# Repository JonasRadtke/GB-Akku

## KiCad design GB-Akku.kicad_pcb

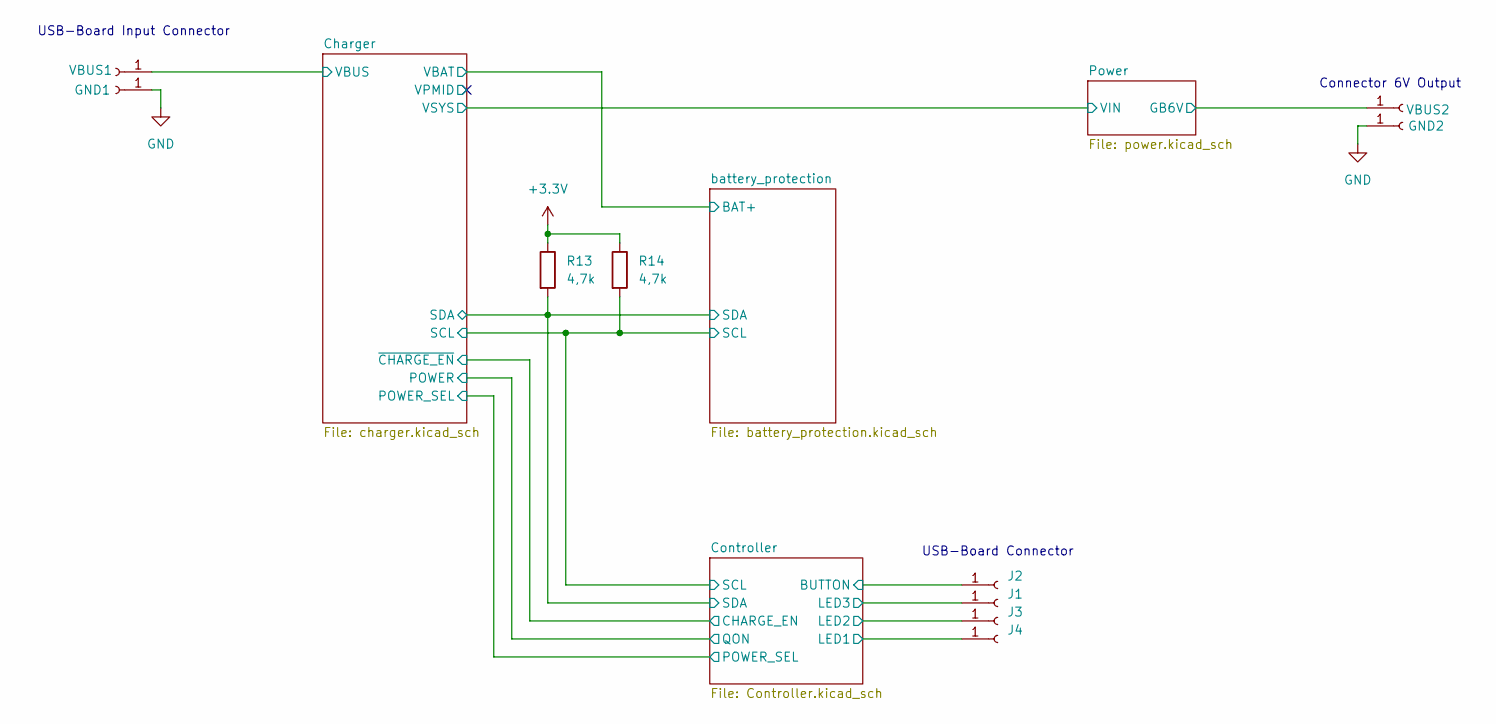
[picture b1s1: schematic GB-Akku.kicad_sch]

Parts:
GND1, GND2: +; SolderWire-0.25sqmm_1x01_D0.65mm_OD1.7mm
J1, J2, J3, J4: Conn_01x01_Socket; SolderWire-0.1sqmm_1x01_D0.4mm_OD1mm
R13, R14: 4,7k; R_0603_1608Metric
VBUS1, VBUS2: +; SolderWire-0.25sqmm_1x01_D0.65mm_OD1.7mm

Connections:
+3.3V: R13.1, R14.1; also elsewhere on the board
+6V: VBUS2.1; also elsewhere on the board
/Charger/SCL: R14.2; also elsewhere on the board
/Charger/SDA: R13.2; also elsewhere on the board
/Charger/VBUS: VBUS1.1; also elsewhere on the board
/Controller/BUTTON: J2.1; also elsewhere on the board
/Controller/LED1: J4.1; also elsewhere on the board
/Controller/LED2: J3.1; also elsewhere on the board
/Controller/LED3: J1.1; also elsewhere on the board
GND: GND1.1, GND2.1; also elsewhere on the board

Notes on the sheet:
Connector 6V Output
USB-Board Input Connector
USB-Board Connector

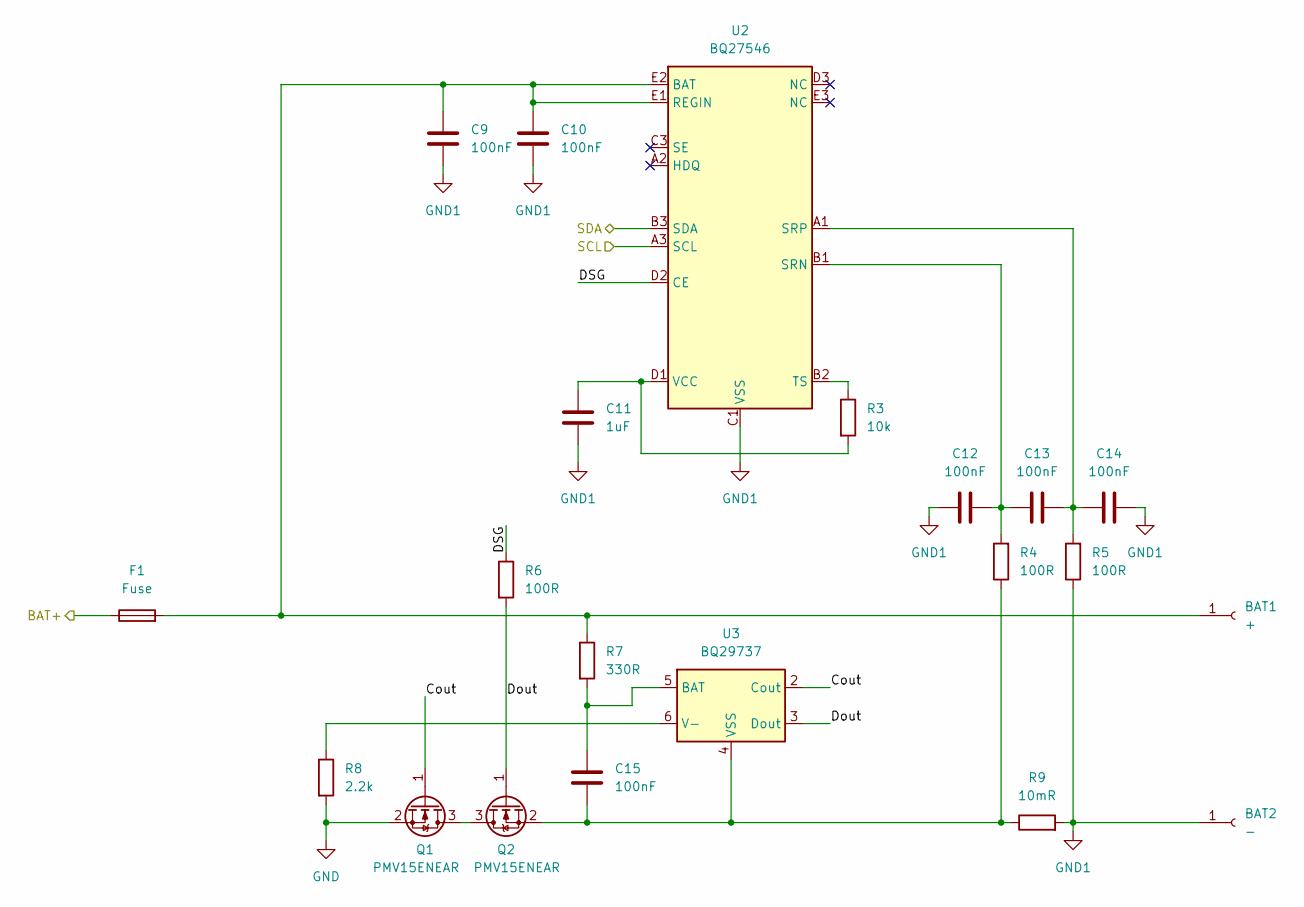
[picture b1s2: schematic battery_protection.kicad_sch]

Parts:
BAT1: +; SolderWire-0.5sqmm_1x01_D0.9mm_OD2.1mm
BAT2: -; SolderWire-0.5sqmm_1x01_D0.9mm_OD2.1mm
C9, C10, C12, C13, C14, C15: 100nF; C_0603_1608Metric
C11: 1uF; C_0603_1608Metric
F1: Fuse; Fuse_1206_3216Metric
Q1, Q2: PMV15ENEAR; SOT-23
R3: 10k; R_0603_1608Metric
R4, R5, R6: 100R; R_0603_1608Metric
R7: 330R; R_0603_1608Metric
R8: 2.2k; R_0603_1608Metric
R9: 10mR; R_0805_2012Metric
U2: BQ27546; DSBGA-15_1.95x2.6mm_P0.5mm_special
U3: BQ29737; WSON-6_1.5x1.5mm_P0.5mm

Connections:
/Charger/SCL: U2.A3 (SCL); also elsewhere on the board
/Charger/SDA: U2.B3 (SDA); also elsewhere on the board
/battery_protection/Cout: Q1.1 (G), U3.2 (Cout)
/battery_protection/DSG: R6.1, U2.D2 (CE)
/battery_protection/Dout: Q2.1 (G), R6.2, U3.3 (Dout)
BAT: F1.1; also elsewhere on the board
GND: Q1.2 (S), R8.2; also elsewhere on the board
GND1: BAT2.1, C9.2, C10.2, C11.2, C12.1, C14.2, R5.1, R9.2, U2.C1 (VSS), U2.C2 (VSS)
unnamed: BAT1.1, C9.1, C10.1, F1.2, R7.1, U2.E1 (REGIN), U2.E2 (BAT)
unnamed: Q1.3 (D), Q2.3 (D)
unnamed: C15.2, Q2.2 (S), R4.1, R9.1, U3.4 (VSS)
unnamed: C12.2, C13.1, R4.2, U2.B1 (SRN)
unnamed: C13.2, C14.1, R5.2, U2.A1 (SRP)
unnamed: R3.1, U2.B2 (TS)
unnamed: C11.1, R3.2, U2.D1 (VCC)
unnamed: C15.1, R7.2, U3.5 (BAT)
unnamed: R8.1, U3.6 (V-)

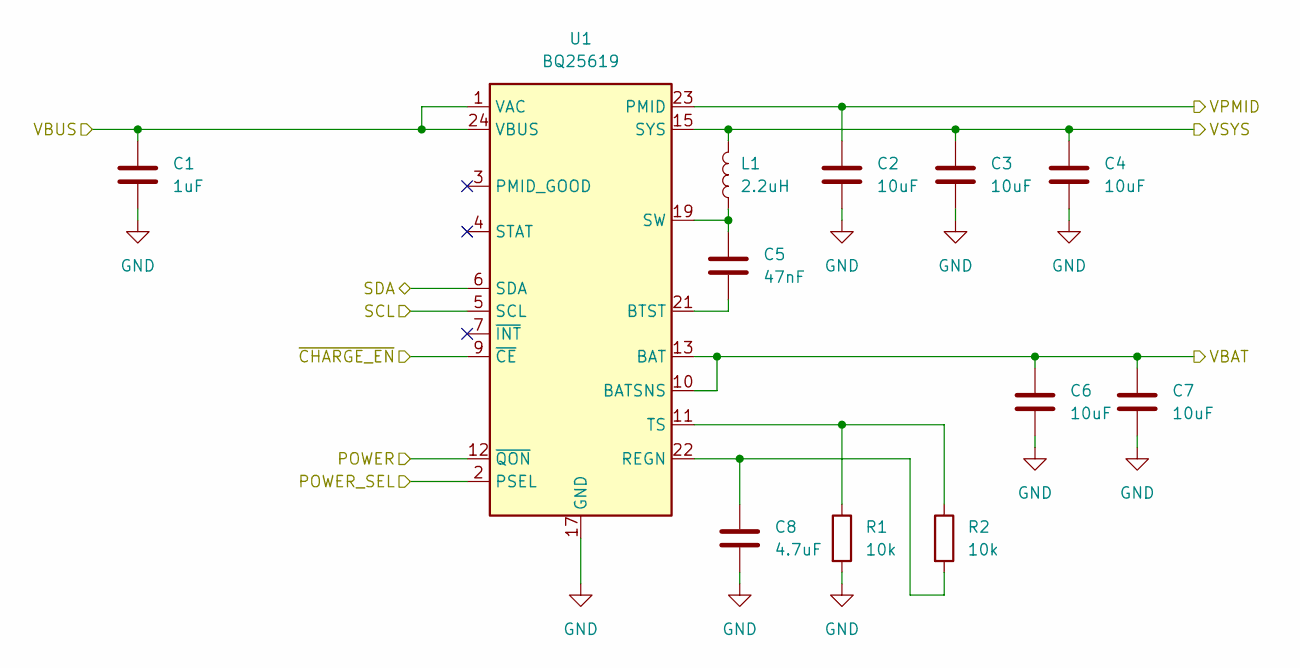
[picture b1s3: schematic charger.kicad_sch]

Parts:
C1: 1uF; C_0603_1608Metric
C2, C3, C4, C6, C7: 10uF; C_0603_1608Metric
C5: 47nF; C_0603_1608Metric
C8: 4.7uF; C_0603_1608Metric
L1: 2.2uH; L_Vishay_IHLP-1616
R1, R2: 10k; R_0603_1608Metric
U1: BQ25619; WQFN-24-1EP_4x4mm_P0.5mm_EP2.6x2.6mm_ThermalVias

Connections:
/Charger/POWER: U1.12 (~QON); also elsewhere on the board
/Charger/POWER_SEL: U1.2 (PSEL); also elsewhere on the board
/Charger/SCL: U1.5 (SCL); also elsewhere on the board
/Charger/SDA: U1.6 (SDA); also elsewhere on the board
/Charger/VBUS: C1.1, U1.1 (VAC), U1.24 (VBUS); also elsewhere on the board
/Charger/VPMID: C2.1, U1.23 (PMID)
/Charger/VSYS: C3.1, C4.1, L1.2, U1.15 (SYS), U1.16 (SYS); also elsewhere on the board
/Charger/~CHARGE_EN: U1.9 (~CE); also elsewhere on the board
BAT: C6.1, C7.1, U1.10 (BATSNS), U1.13 (BAT), U1.14 (BAT); also elsewhere on the board
GND: C1.2, C2.2, C3.2, C4.2, C6.2, C7.2, C8.2, R1.2, U1.17 (GND), U1.18 (GND), U1.25 (GND); also elsewhere on the board
unnamed: C5.1, L1.1, U1.19 (SW), U1.20 (SW)
unnamed: C5.2, U1.21 (BTST)
unnamed: C8.1, R2.2, U1.22 (REGN)
unnamed: R1.1, R2.1, U1.11 (TS)

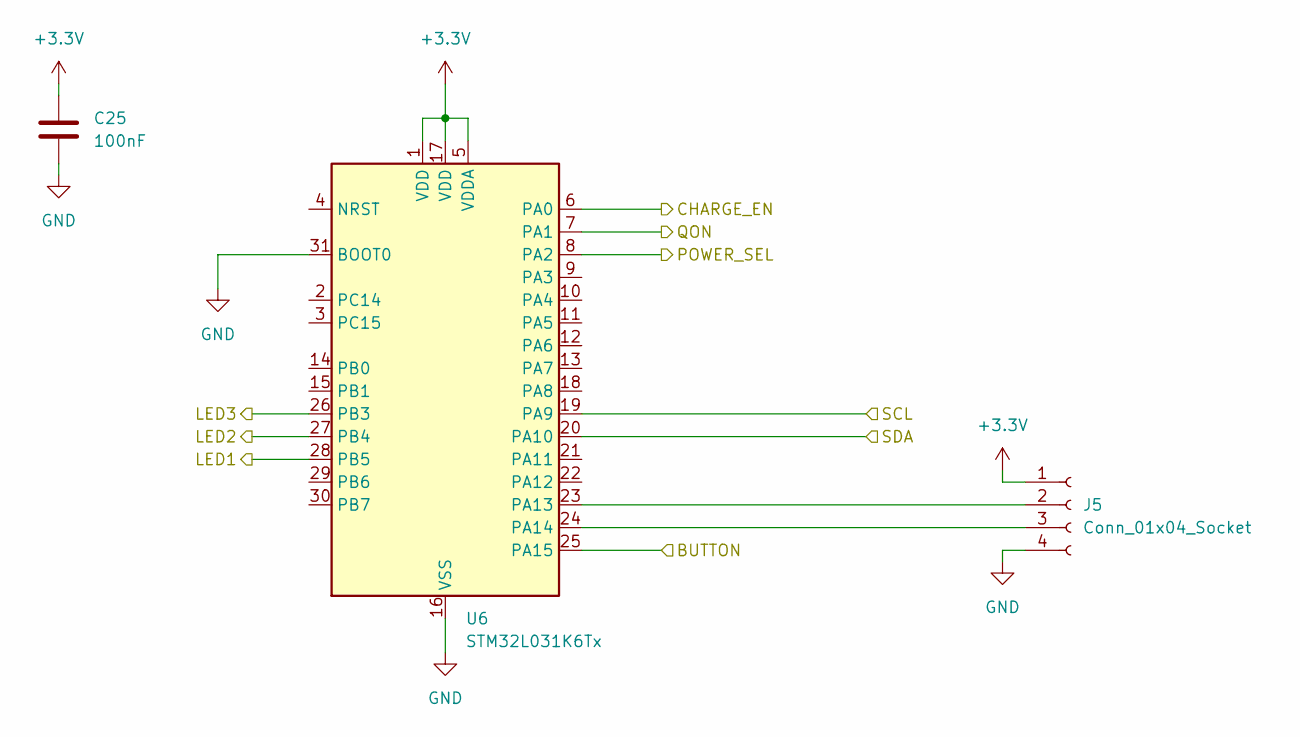
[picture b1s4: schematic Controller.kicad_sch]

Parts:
C25: 100nF; C_0603_1608Metric
J5: Conn_01x04_Socket; PinHeader_1x04_P2.54mm_Vertical
U6: STM32L031K6Tx; LQFP-32_7x7mm_P0.8mm

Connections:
+3.3V: C25.1, J5.1, U6.1 (VDD), U6.5 (VDDA), U6.17 (VDD); also elsewhere on the board
/Charger/POWER: U6.7 (PA1); also elsewhere on the board
/Charger/POWER_SEL: U6.8 (PA2); also elsewhere on the board
/Charger/SCL: U6.19 (PA9); also elsewhere on the board
/Charger/SDA: U6.20 (PA10); also elsewhere on the board
/Charger/~CHARGE_EN: U6.6 (PA0); also elsewhere on the board
/Controller/BUTTON: U6.25 (PA15); also elsewhere on the board
/Controller/LED1: U6.28 (PB5); also elsewhere on the board
/Controller/LED2: U6.27 (PB4); also elsewhere on the board
/Controller/LED3: U6.26 (PB3); also elsewhere on the board
GND: C25.2, J5.4, U6.16 (VSS), U6.31 (BOOT0), U6.32 (VSS); also elsewhere on the board
unnamed: J5.2, U6.23 (PA13)
unnamed: J5.3, U6.24 (PA14)

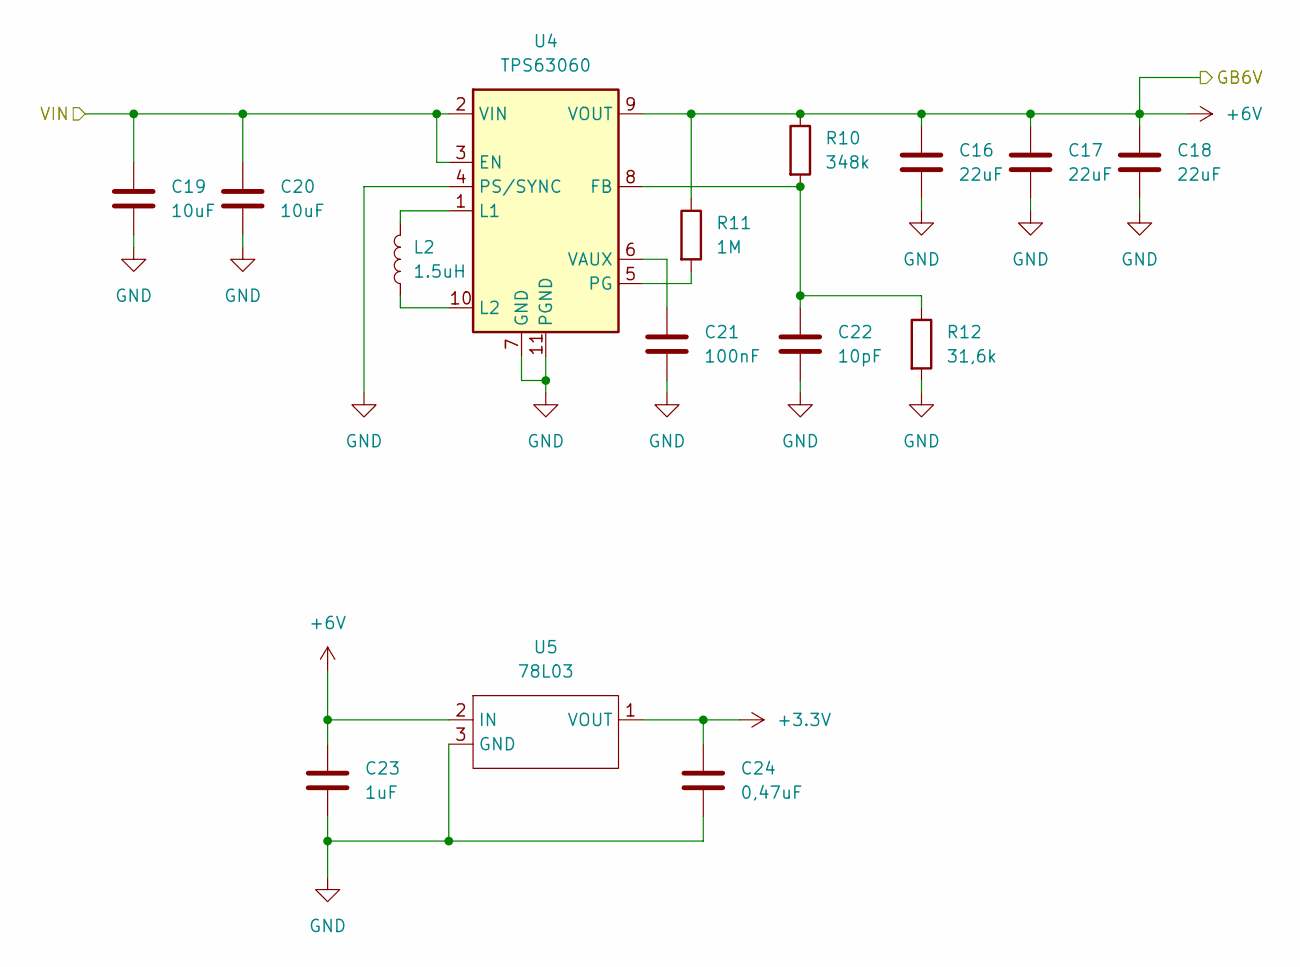
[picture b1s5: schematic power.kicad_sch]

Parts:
C16, C17, C18: 22uF; C_0603_1608Metric
C19, C20: 10uF; C_0603_1608Metric
C21: 100nF; C_0603_1608Metric
C22: 10pF; C_0603_1608Metric
C23: 1uF; C_0603_1608Metric
C24: 0,47uF; C_0603_1608Metric
L2: 1.5uH; L_Vishay_IHLP-1616
R10: 348k; R_0603_1608Metric
R11: 1M; R_0603_1608Metric
R12: 31,6k; R_0603_1608Metric
U4: TPS63060; Texas_S-PWSON-N10_ThermalVias
U5: 78L03; SOT-23-3

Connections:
+3.3V: C24.1, U5.1 (VOUT); also elsewhere on the board
+6V: C16.1, C17.1, C18.1, C23.1, R10.1, R11.1, U4.9 (VOUT), U5.2 (IN); also elsewhere on the board
/Charger/VSYS: C19.1, C20.1, U4.2 (VIN), U4.3 (EN); also elsewhere on the board
GND: C16.2, C17.2, C18.2, C19.2, C20.2, C21.2, C22.2, C23.2, C24.2, R12.2, U4.4 (PS/SYNC), U4.7 (GND), U4.11 (PGND), U5.3 (GND); also elsewhere on the board
unnamed: C22.1, R10.2, R12.1, U4.8 (FB)
unnamed: L2.2, U4.1 (L1)
unnamed: L2.1, U4.10 (L2)
unnamed: R11.2, U4.5 (PG)
unnamed: C21.1, U4.6 (VAUX)

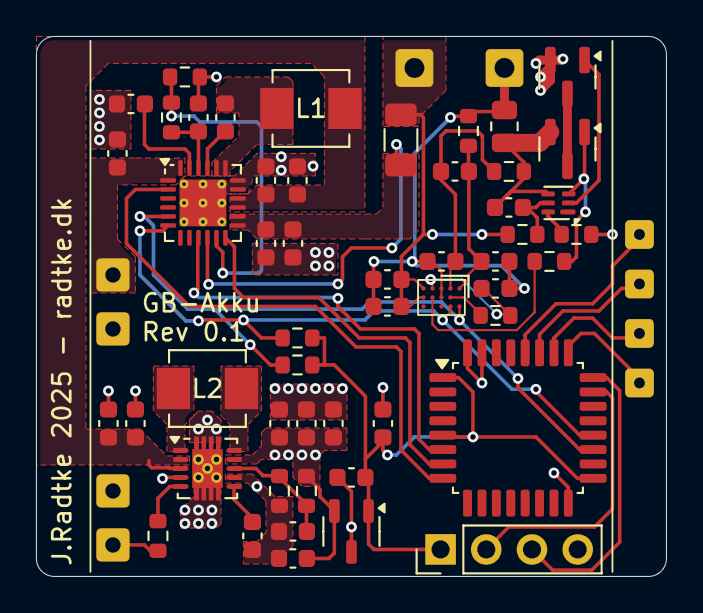
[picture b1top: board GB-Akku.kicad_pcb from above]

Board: 2 copper layers, 35.0 x 30.0 mm, 61 parts (0 on the bottom side), 40 nets.

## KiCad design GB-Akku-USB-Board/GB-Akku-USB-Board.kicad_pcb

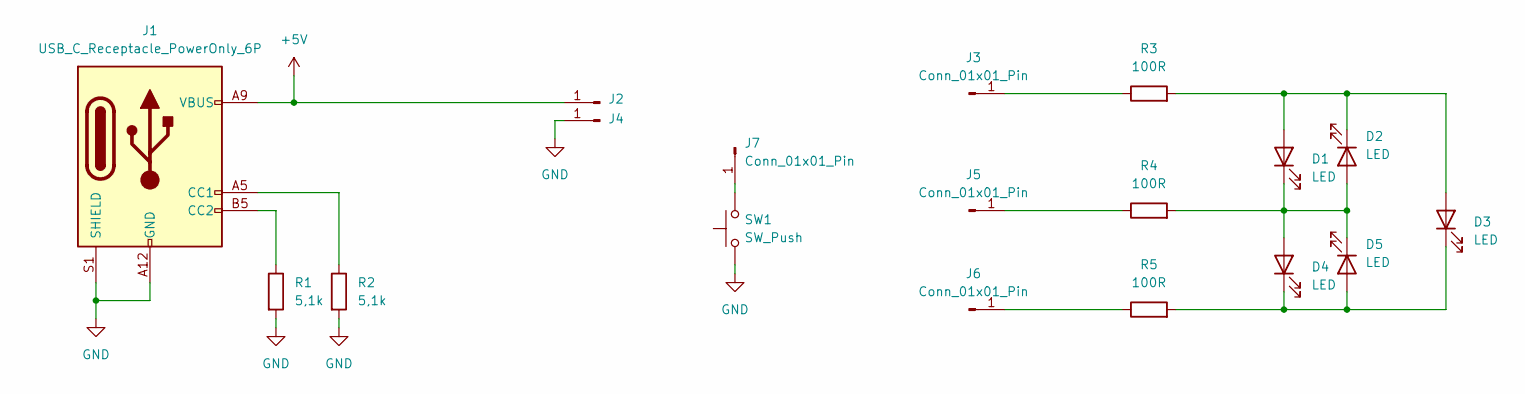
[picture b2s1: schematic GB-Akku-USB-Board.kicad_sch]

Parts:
D1, D2, D3, D4, D5: LED; LED_0805_2012Metric
J1: USB_C_Receptacle_PowerOnly_6P; UJC-V-G-SMT-P6-TR
J2, J4: Conn_01x01_Pin; SolderWire-0.5sqmm_1x01_D0.9mm_OD2.1mm
J3, J5, J6, J7: Conn_01x01_Pin; SolderWire-0.1sqmm_1x01_D0.4mm_OD1mm
R1, R2: 5,1k; R_0603_1608Metric
R3, R4, R5: 100R; R_0603_1608Metric
SW1: SW_Push; TL1017AABF260QG

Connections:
+5V: J1.A9 (VBUS), J1.B9 (VBUS), J2.1
GND: J1.A12 (GND), J1.B12 (GND), J1.S1 (SHIELD), J4.1, R1.2, R2.2, SW1.1
unnamed: D1.2 (A), D2.1 (K), D3.2 (A), R3.2
unnamed: D1.1 (K), D2.2 (A), D4.2 (A), D5.1 (K), R4.2
unnamed: D3.1 (K), D4.1 (K), D5.2 (A), R5.2
unnamed: J1.A5 (CC1), R2.1
unnamed: J1.B5 (CC2), R1.1
unnamed: J3.1, R3.1
unnamed: J5.1, R4.1
unnamed: J6.1, R5.1
unnamed: J7.1, SW1.2

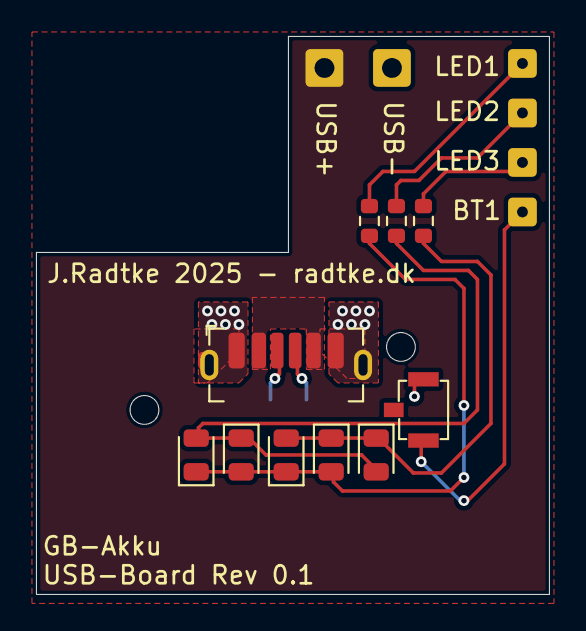
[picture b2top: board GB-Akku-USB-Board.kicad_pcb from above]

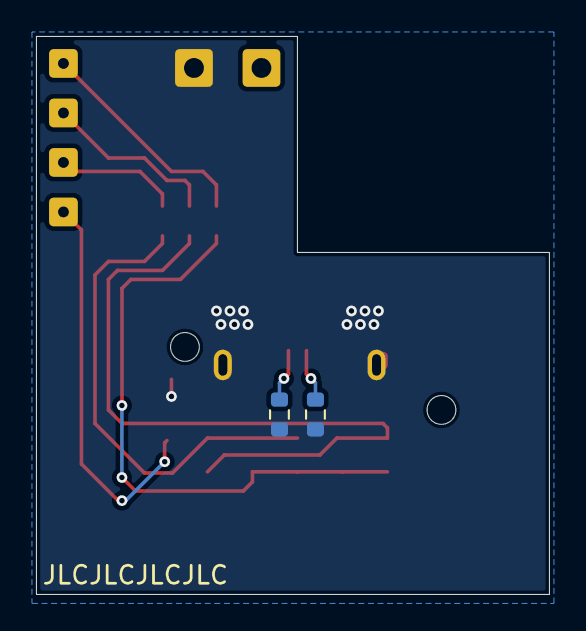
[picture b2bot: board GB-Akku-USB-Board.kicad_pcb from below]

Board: 2 copper layers, 28.5 x 31.0 mm, 18 parts (2 on the bottom side), 11 nets.

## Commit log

2025-01-26 Rev 0.1
    first order
2025-02-14 STM32 BOOT0 Pin fixed
2025-02-21 pictures
